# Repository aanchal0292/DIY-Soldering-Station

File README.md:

# DIY-Soldering-Station
# Sibu's Soldering Station Documentation

All of the documentations unless specified within the file or directory, is licensed under [CC-BY-SA](https://creativecommons.org/licenses/by-sa/4.0/legalcode) except for the source codes, which are licensed under [GPLv3](https://www.gnu.org/licenses/quick-guide-gplv3.en.html).

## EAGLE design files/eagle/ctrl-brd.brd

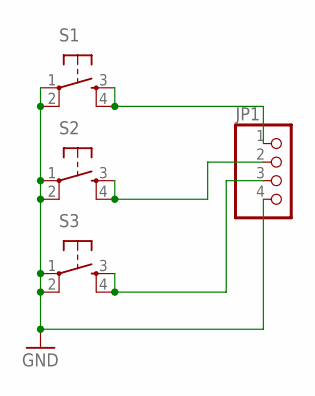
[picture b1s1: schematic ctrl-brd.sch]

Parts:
JP1: PINHD-1X4; 1X04
S1, S2, S3: 6MM_SWITCH6MM_SWITCH; 6MM_SWITCH

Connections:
GND: JP1.4, S1.1, S1.2 (P1), S2.1, S2.2 (P1), S3.1, S3.2 (P1)
unnamed: JP1.1, S1.3 (S), S1.4 (S1)
unnamed: JP1.2, S2.3 (S), S2.4 (S1)
unnamed: JP1.3, S3.3 (S), S3.4 (S1)

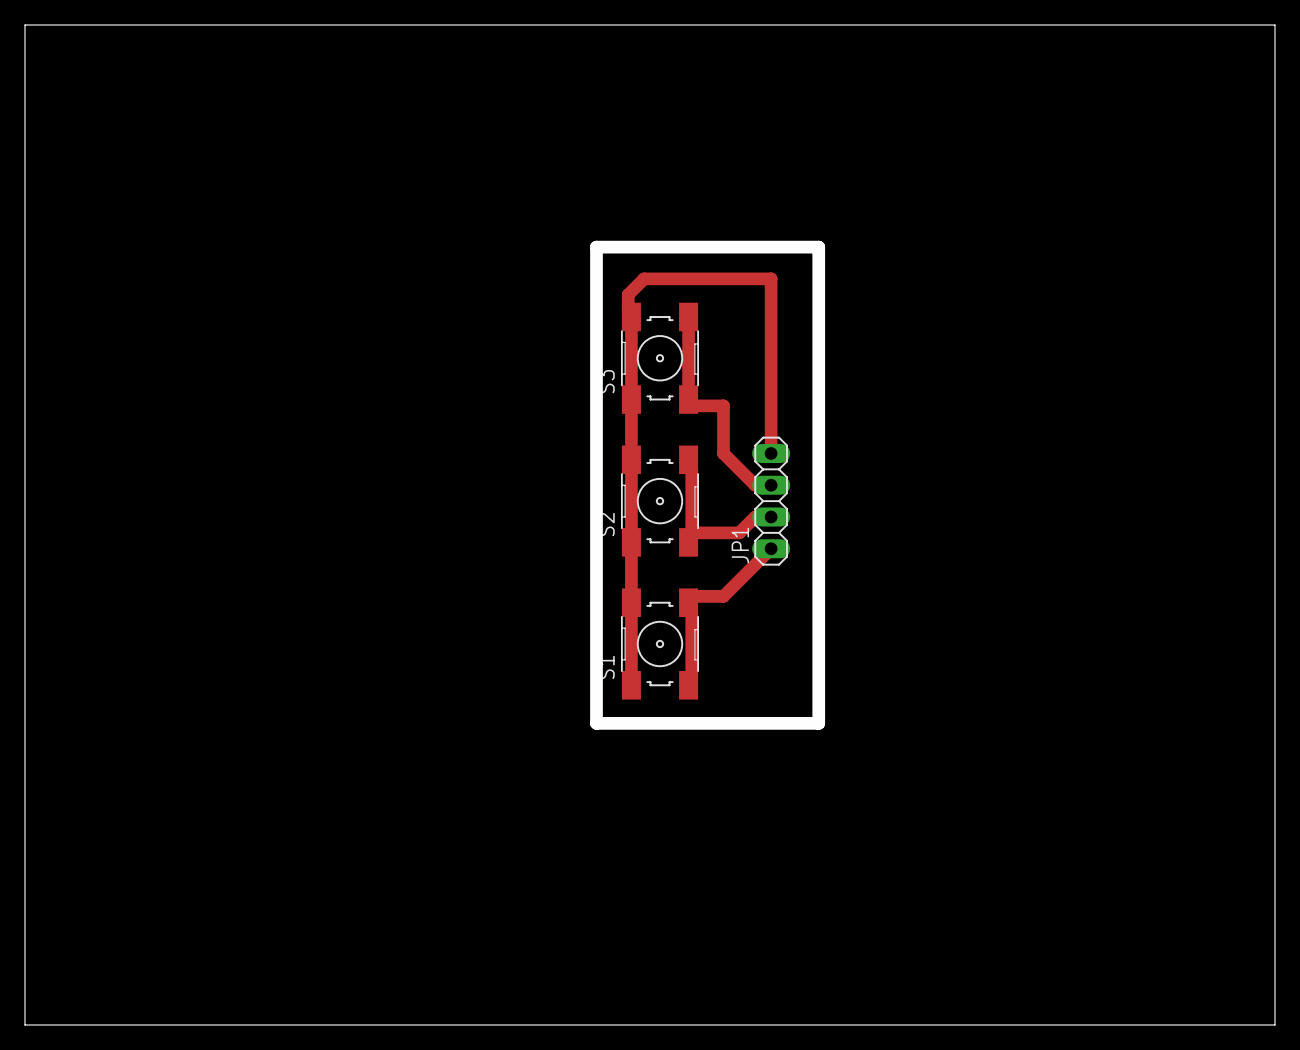
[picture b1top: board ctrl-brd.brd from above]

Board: 2 copper layers, 100.0 x 80.0 mm, 4 parts (0 on the bottom side), 4 nets.

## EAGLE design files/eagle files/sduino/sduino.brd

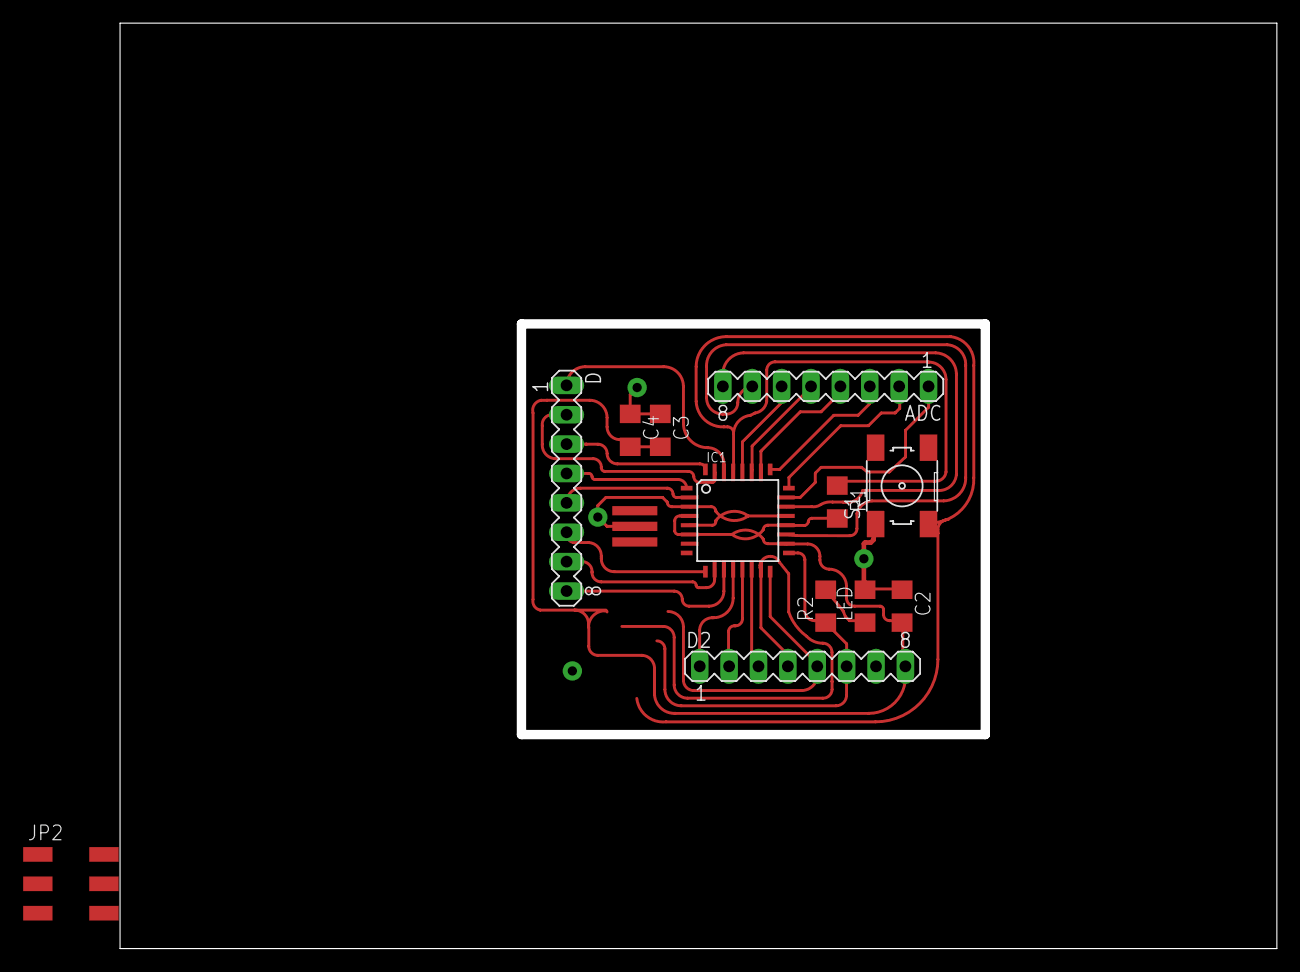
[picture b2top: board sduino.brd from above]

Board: 2 copper layers, 100.0 x 80.0 mm, 13 parts (0 on the bottom side), 28 nets.

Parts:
ADC: MA08-1
C2: 1uf; 1206
C3: .1uf; 1206
C4: 10uf; 1206
D, D2: MA08-1
IC1: ATMEGA48/88/168-AU; TQFP32-08
JP2: 2X03SMD
LED: 1206
R1: 10k; 1206
R2: 499; 1206
S1: 6MM_SWITCH
U$2: RESONATOREFOB; EFOBM

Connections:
GND: C2.1, C3.1, C4.1, D2.7, IC1.3, IC1.5, IC1.21, JP2.6, LED.2, S1.1, U$2.2
MISO: D2.5, IC1.16, JP2.1
MOSI: D2.4, IC1.15, JP2.4
unnamed: IC1.7, U$2.1
unnamed: D2.1, IC1.12
unnamed: ADC.1, IC1.23
unnamed: ADC.2, IC1.24
unnamed: ADC.3, IC1.25
unnamed: ADC.4, IC1.26
unnamed: ADC.5, IC1.27
unnamed: ADC.6, IC1.28
unnamed: D.3, IC1.32
unnamed: D.4, IC1.1
unnamed: D.5, IC1.2
unnamed: D.6, IC1.9
unnamed: D.7, IC1.10
unnamed: D.8, IC1.11
unnamed: IC1.8, U$2.3
unnamed: D2.2, IC1.13
unnamed: D2.3, IC1.14
unnamed: ADC.7, IC1.19
unnamed: ADC.8, IC1.22
unnamed: LED.1, R2.2
RST: IC1.29, JP2.5, R1.1, S1.3
RX: D.1, IC1.30
SCK: D2.6, IC1.17, JP2.3, R2.1
TX: D.2, IC1.31
VCC: C2.2, C3.2, C4.2, D2.8, IC1.4, IC1.6, IC1.18, IC1.20, JP2.2, R1.2

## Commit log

2015-11-19 few pics
2015-11-19 few more pics
2015-11-20 typo in heading
2015-11-20 code
2015-11-20 Deleted files manually
2015-11-27 edits
2016-02-15 fixing image display option
2016-03-05 typo
2016-07-04 Update LICENSE
2019-07-10 test
2019-07-10 test2
